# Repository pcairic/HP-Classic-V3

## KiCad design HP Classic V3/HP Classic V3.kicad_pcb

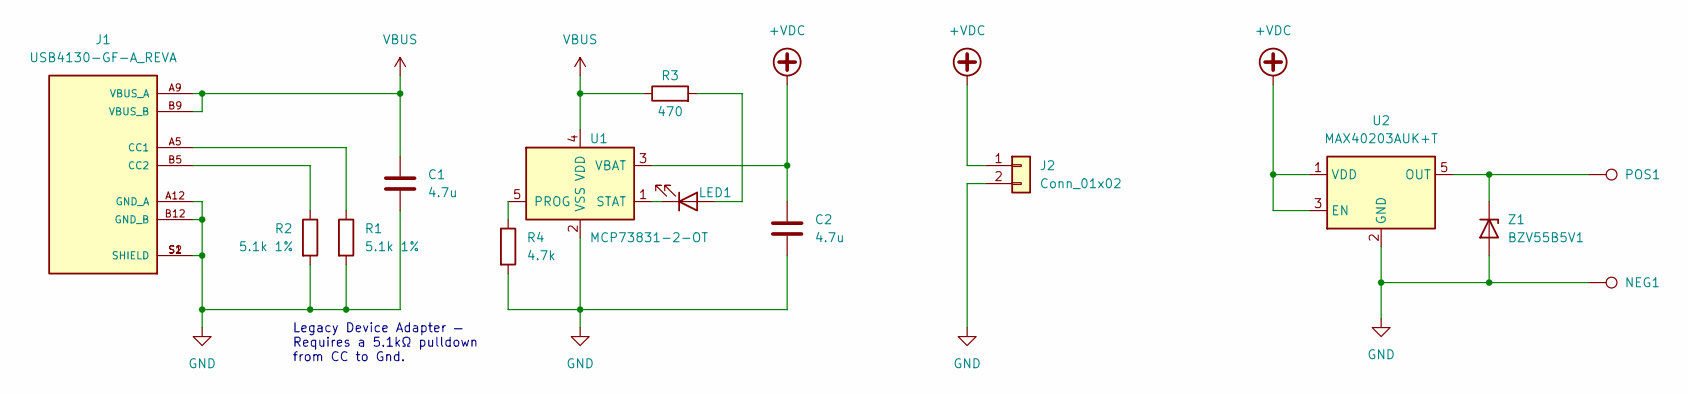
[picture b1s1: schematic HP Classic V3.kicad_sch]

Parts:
C1, C2: 4.7u; C_0805_2012Metric_Pad1.18x1.45mm_HandSolder
J1: USB4130-GF-A_REVA; GCT_USB4130-GF-A_REVA; PARTREV A
J2: Conn_01x02; JST_PH_S2B-PH-K_1x02_P2.00mm_Horizontal
LED1: LED; LED_0805_2012Metric_Pad1.15x1.40mm_HandSolder
NEG1: TestPoint; HP Classic PAD
POS1: TestPoint; HP Classic PAD
R1, R2: 5.1k 1%; R_0805_2012Metric_Pad1.20x1.40mm_HandSolder
R3: 470; R_0805_2012Metric_Pad1.20x1.40mm_HandSolder
R4: 4.7k; R_0805_2012Metric_Pad1.20x1.40mm_HandSolder
U1: MCP73831-2-OT; SOT-23-5
U2: MAX40203AUK+T; SOT-23-5
Z1: BZV55B5V1; D_MiniMELF

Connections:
+VDC: C2.1, J2.1, U1.3 (VBAT), U2.1 (VDD), U2.3 (EN)
GND: C1.2, C2.2, J1.A12 (GND_A), J1.B12 (GND_B), J1.S1 (SHIELD), J1.S2 (SHIELD), J2.2, NEG1.1, R1.2, R2.2, R4.2, U1.2 (VSS), U2.2 (GND), Z1.2 (A)
unnamed: J1.A5 (CC1), R1.1
unnamed: J1.B5 (CC2), R2.1
unnamed: LED1.1 (K), U1.1 (STAT)
unnamed: LED1.2 (A), R3.2
unnamed: POS1.1, U2.5 (OUT), Z1.1 (K)
unnamed: R4.1, U1.5 (PROG)
VBUS: C1.1, J1.A9 (VBUS_A), J1.B9 (VBUS_B), R3.1, U1.4 (VDD)

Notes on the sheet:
Legacy Device Adapter — Requires a 5.1kΩ pulldown from CC to Gnd.

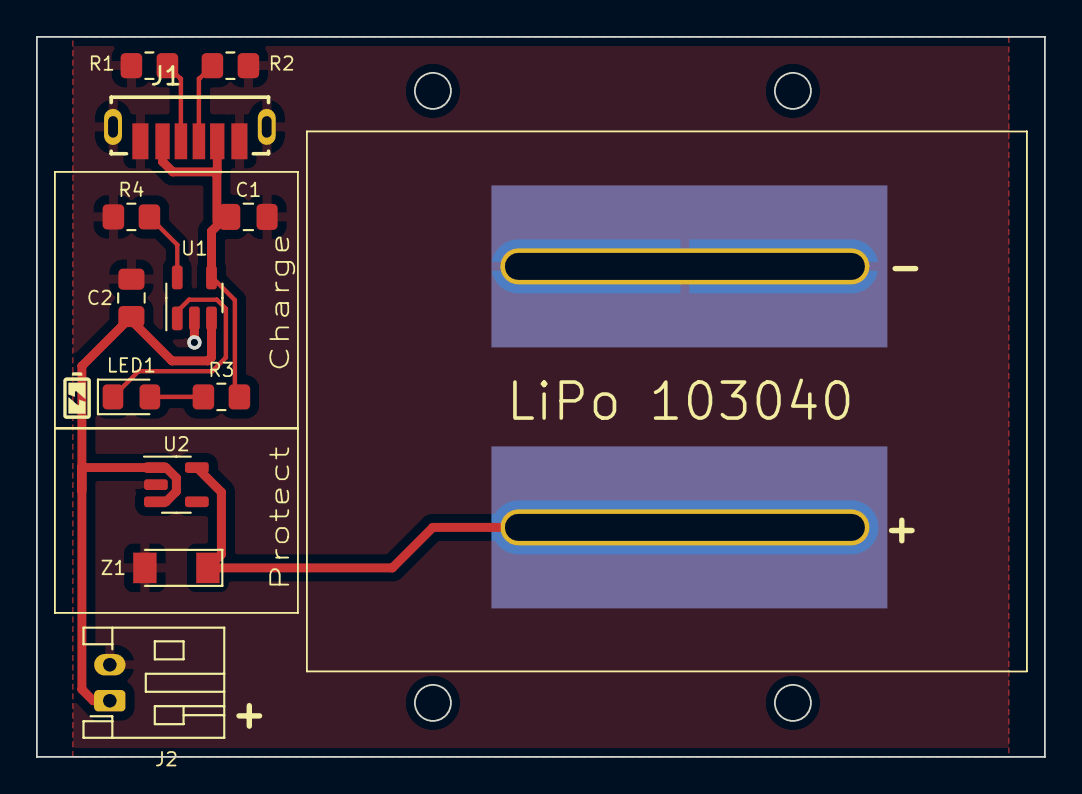
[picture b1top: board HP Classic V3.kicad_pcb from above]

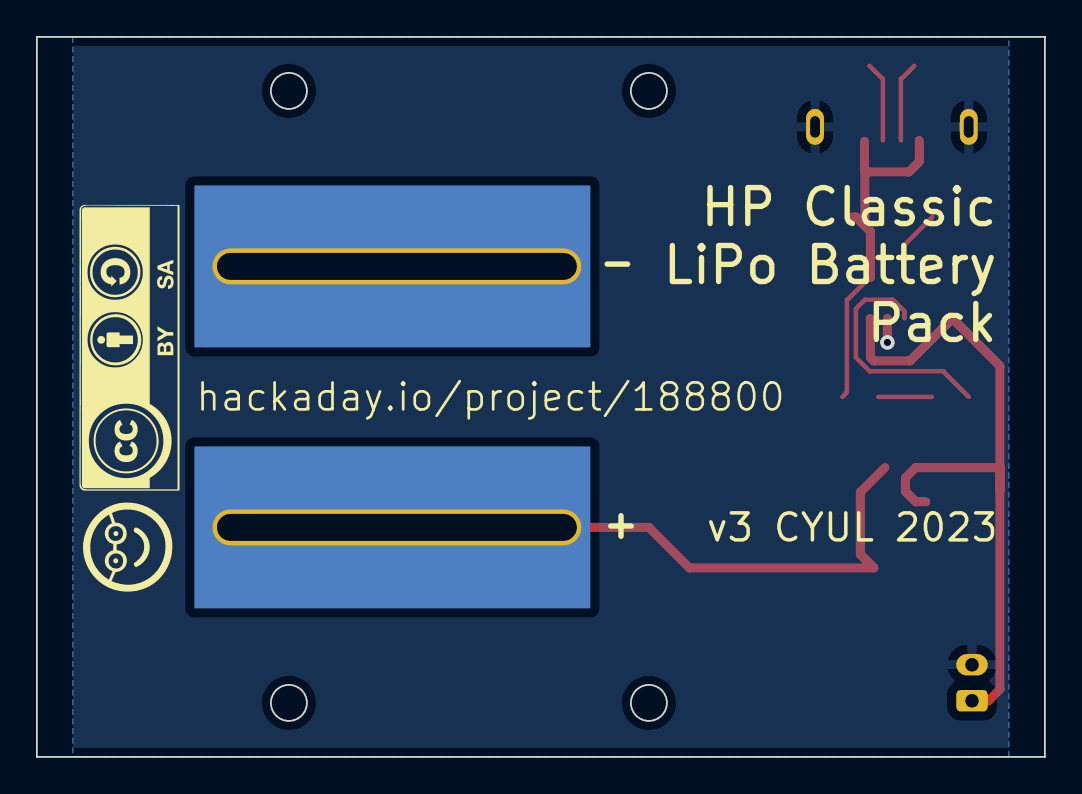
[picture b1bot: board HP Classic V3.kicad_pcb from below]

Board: 2 copper layers, 56.0 x 40.0 mm, 14 parts (2 on the bottom side), 9 nets.

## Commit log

2023-02-04 Initial commit of the electronics
2023-02-04 3D models of the case and PCB
    https://www.tinkercad.com/things/0ijeQJ1wLGP
